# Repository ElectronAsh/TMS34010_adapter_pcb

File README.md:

# TMS34010_adapter_pcb

# USE AT YOUR OWN RISK!

This adapter PCB should allow you to connect a TMS34010 CPU to FPGA dev boards like the DE10 Nano, and maybe the DE0.

But it is currently UNTESTED, and does not include proper voltage translation buffers between 3V3 and 5V.

The current design only has some series resistors on each CPU output pin, with some clamp diodes on the FPGA GPIO headers.

There is an inherent risk of not using proper voltage translation, but I would personally risk it for short-term use for development.

If I get time, I will add proper voltage translation to the board.
The current design was just a way to get a quick version done for the few devs who might be able to make use of it.

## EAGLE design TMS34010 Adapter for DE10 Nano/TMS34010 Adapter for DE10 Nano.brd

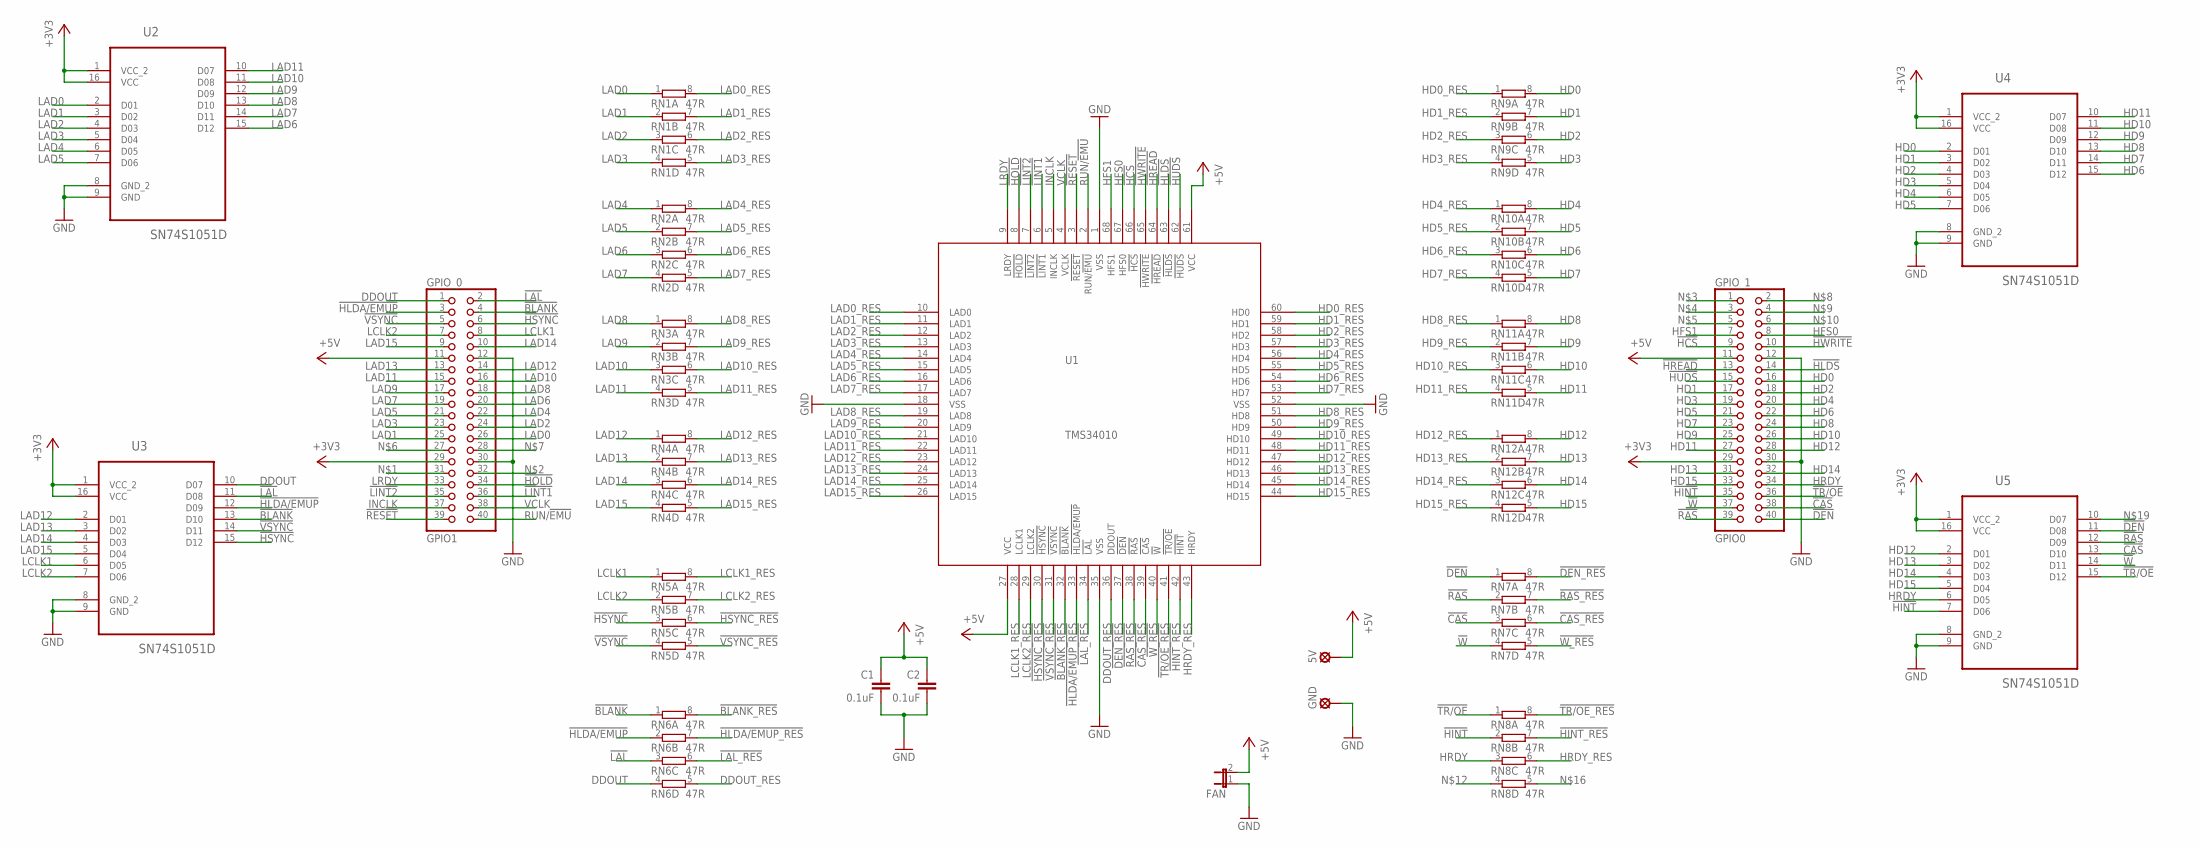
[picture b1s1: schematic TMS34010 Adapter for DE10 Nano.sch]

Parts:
5V: LSP13
C1, C2: 0.1uF; C0603
FAN: JP1E; JP1
GND: LSP13
GPIO_0: GPIO1; 2X20
GPIO_1: GPIO0; 2X20
RN1, RN2, RN3, RN4, RN5, RN6, RN7, RN8, RN9, RN10, RN11, RN12: 47R; EXBV8V
U1: TMS34010; PLCC68
U2, U3, U4, U5: SN74S1051D; SOIC127P600X175-16N

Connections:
!BLANK: GPIO_0.4, RN6.1, U3.13 (D10)
!BLANK_RES: RN6.8 (2), U1.32 (!BLANK)
!CAS: GPIO_1.38, RN7.3 (1), U5.13 (D10)
!CAS_RES: RN7.6 (2), U1.39 (!CAS)
!DEN: GPIO_1.40, RN7.1, U5.11 (D08)
!DEN_RES: RN7.8 (2), U1.37 (!DEN)
!HCS: GPIO_1.9, U1.66 (!HCS)
!HINT: GPIO_1.35, RN8.2 (1), U5.7 (D06)
!HINT_RES: RN8.7 (2), U1.42 (!HINT)
!HLDA/EMUP: GPIO_0.3, RN6.2 (1), U3.12 (D09)
!HLDA/EMUP_RES: RN6.7 (2), U1.33 (!HLDA/EMUP)
!HLDS: GPIO_1.14, U1.63 (!HLDS)
!HOLD: GPIO_0.34, U1.8 (!HOLD)
!HREAD: GPIO_1.13, U1.64 (!HREAD)
!HSYNC: GPIO_0.6, RN5.3 (1), U3.15 (D12)
!HSYNC_RES: RN5.6 (2), U1.30 (!HSYNC)
!HUDS: GPIO_1.15, U1.62 (!HUDS)
!HWRITE: GPIO_1.10, U1.65 (!HWRITE)
!LAL: GPIO_0.2, RN6.3 (1), U3.11 (D08)
!LAL_RES: RN6.6 (2), U1.34 (!LAL)
!LINT1: GPIO_0.36, U1.6 (!LINT1)
!LINT2: GPIO_0.35, U1.7 (!LINT2)
!RAS: GPIO_1.39, RN7.2 (1), U5.12 (D09)
!RAS_RES: RN7.7 (2), U1.38 (!RAS)
!RESET: GPIO_0.39, U1.3 (!RESET)
!TR/OE: GPIO_1.36, RN8.1, U5.15 (D12)
!TR/OE_RES: RN8.8 (2), U1.41 (!TR/OE)
!VSYNC: GPIO_0.5, RN5.4 (1), U3.14 (D11)
!VSYNC_RES: RN5.5 (2), U1.31 (!VSYNC)
!W: GPIO_1.37, RN7.4 (1), U5.14 (D11)
!W_RES: RN7.5 (2), U1.40 (!W)
+3V3: GPIO_0.29, GPIO_1.29, U2.1 (VCC_2), U2.16 (VCC), U3.1 (VCC_2), U3.16 (VCC), U4.1 (VCC_2), U4.16 (VCC), U5.1 (VCC_2), U5.16 (VCC)
+5V: 5V.MP, C1.1, C2.1, FAN.2, GPIO_0.11, GPIO_1.11, U1.27 (VCC), U1.61 (VCC)
DDOUT: GPIO_0.1, RN6.4 (1), U3.10 (D07)
DDOUT_RES: RN6.5 (2), U1.36 (DDOUT)
GND: C1.2, C2.2, FAN.1, GND.MP, GPIO_0.12, GPIO_0.30, GPIO_1.12, GPIO_1.30, U1.1 (VSS), U1.18 (VSS), U1.35 (VSS), U1.52 (VSS), U2.8 (GND_2), U2.9 (GND), U3.8 (GND_2), U3.9 (GND), U4.8 (GND_2), U4.9 (GND), U5.8 (GND_2), U5.9 (GND)
HD0: GPIO_1.16, RN9.8 (2), U4.2 (D01)
HD0_RES: RN9.1, U1.60 (HD0)
HD1: GPIO_1.17, RN9.7 (2), U4.3 (D02)
HD1_RES: RN9.2 (1), U1.59 (HD1)
HD2: GPIO_1.18, RN9.6 (2), U4.4 (D03)
HD2_RES: RN9.3 (1), U1.58 (HD2)
HD3: GPIO_1.19, RN9.5 (2), U4.5 (D04)
HD3_RES: RN9.4 (1), U1.57 (HD3)
HD4: GPIO_1.20, RN10.8 (2), U4.6 (D05)
HD4_RES: RN10.1, U1.56 (HD4)
HD5: GPIO_1.21, RN10.7 (2), U4.7 (D06)
HD5_RES: RN10.2 (1), U1.55 (HD5)
HD6: GPIO_1.22, RN10.6 (2), U4.15 (D12)
HD6_RES: RN10.3 (1), U1.54 (HD6)
HD7: GPIO_1.23, RN10.5 (2), U4.14 (D11)
HD7_RES: RN10.4 (1), U1.53 (HD7)
HD8: GPIO_1.24, RN11.8 (2), U4.13 (D10)
HD8_RES: RN11.1, U1.51 (HD8)
HD9: GPIO_1.25, RN11.7 (2), U4.12 (D09)
HD9_RES: RN11.2 (1), U1.50 (HD9)
HD10: GPIO_1.26, RN11.6 (2), U4.11 (D08)
HD10_RES: RN11.3 (1), U1.49 (HD10)
HD11: GPIO_1.27, RN11.5 (2), U4.10 (D07)
HD11_RES: RN11.4 (1), U1.48 (HD11)
HD12: GPIO_1.28, RN12.8 (2), U5.2 (D01)
HD12_RES: RN12.1, U1.47 (HD12)
HD13: GPIO_1.31, RN12.7 (2), U5.3 (D02)
HD13_RES: RN12.2 (1), U1.46 (HD13)
HD14: GPIO_1.32, RN12.6 (2), U5.4 (D03)
HD14_RES: RN12.3 (1), U1.45 (HD14)
HD15: GPIO_1.33, RN12.5 (2), U5.5 (D04)
HD15_RES: RN12.4 (1), U1.44 (HD15)
HFS0: GPIO_1.8, U1.67 (HFS0)
HFS1: GPIO_1.7, U1.68 (HFS1)
HRDY: GPIO_1.34, RN8.3 (1), U5.6 (D05)
HRDY_RES: RN8.6 (2), U1.43 (HRDY)
INCLK: GPIO_0.37, U1.5 (INCLK)
LAD0: GPIO_0.26, RN1.1, U2.2 (D01)
LAD0_RES: RN1.8 (2), U1.10 (LAD0)
LAD1: GPIO_0.25, RN1.2 (1), U2.3 (D02)
LAD1_RES: RN1.7 (2), U1.11 (LAD1)
LAD2: GPIO_0.24, RN1.3 (1), U2.4 (D03)
LAD2_RES: RN1.6 (2), U1.12 (LAD2)
LAD3: GPIO_0.23, RN1.4 (1), U2.5 (D04)
LAD3_RES: RN1.5 (2), U1.13 (LAD3)
LAD4: GPIO_0.22, RN2.1, U2.6 (D05)
LAD4_RES: RN2.8 (2), U1.14 (LAD4)
LAD5: GPIO_0.21, RN2.2 (1), U2.7 (D06)
LAD5_RES: RN2.7 (2), U1.15 (LAD5)
LAD6: GPIO_0.20, RN2.3 (1), U2.15 (D12)
LAD6_RES: RN2.6 (2), U1.16 (LAD6)
LAD7: GPIO_0.19, RN2.4 (1), U2.14 (D11)
LAD7_RES: RN2.5 (2), U1.17 (LAD7)
LAD8: GPIO_0.18, RN3.1, U2.13 (D10)
LAD8_RES: RN3.8 (2), U1.19 (LAD8)
LAD9: GPIO_0.17, RN3.2 (1), U2.12 (D09)
LAD9_RES: RN3.7 (2), U1.20 (LAD9)
LAD10: GPIO_0.16, RN3.3 (1), U2.11 (D08)
LAD10_RES: RN3.6 (2), U1.21 (LAD10)
LAD11: GPIO_0.15, RN3.4 (1), U2.10 (D07)
LAD11_RES: RN3.5 (2), U1.22 (LAD11)
LAD12: GPIO_0.14, RN4.1, U3.2 (D01)
LAD12_RES: RN4.8 (2), U1.23 (LAD12)
LAD13: GPIO_0.13, RN4.2 (1), U3.3 (D02)
LAD13_RES: RN4.7 (2), U1.24 (LAD13)
LAD14: GPIO_0.10, RN4.3 (1), U3.4 (D03)
LAD14_RES: RN4.6 (2), U1.25 (LAD14)
LAD15: GPIO_0.9, RN4.4 (1), U3.5 (D04)
LAD15_RES: RN4.5 (2), U1.26 (LAD15)
LCLK1: GPIO_0.8, RN5.1, U3.6 (D05)
LCLK1_RES: RN5.8 (2), U1.28 (LCLK1)
LCLK2: GPIO_0.7, RN5.2 (1), U3.7 (D06)
LCLK2_RES: RN5.7 (2), U1.29 (LCLK2)
LRDY: GPIO_0.33, U1.9 (LRDY)
RUN/!EMU: GPIO_0.40, U1.2 (RUN/!EMU)
VCLK: GPIO_0.38, U1.4 (VCLK)

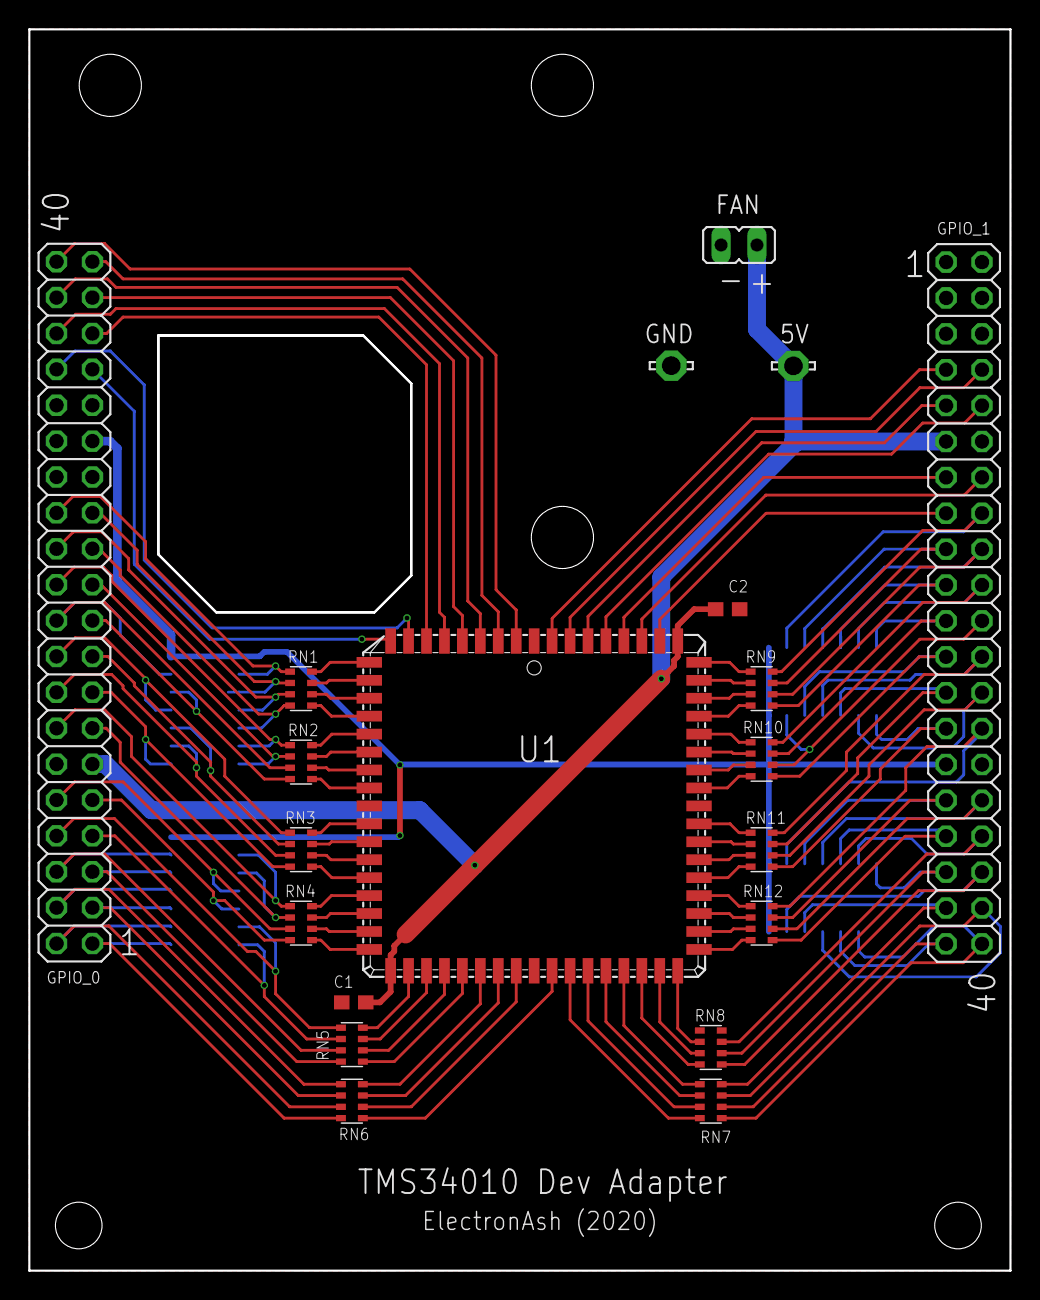
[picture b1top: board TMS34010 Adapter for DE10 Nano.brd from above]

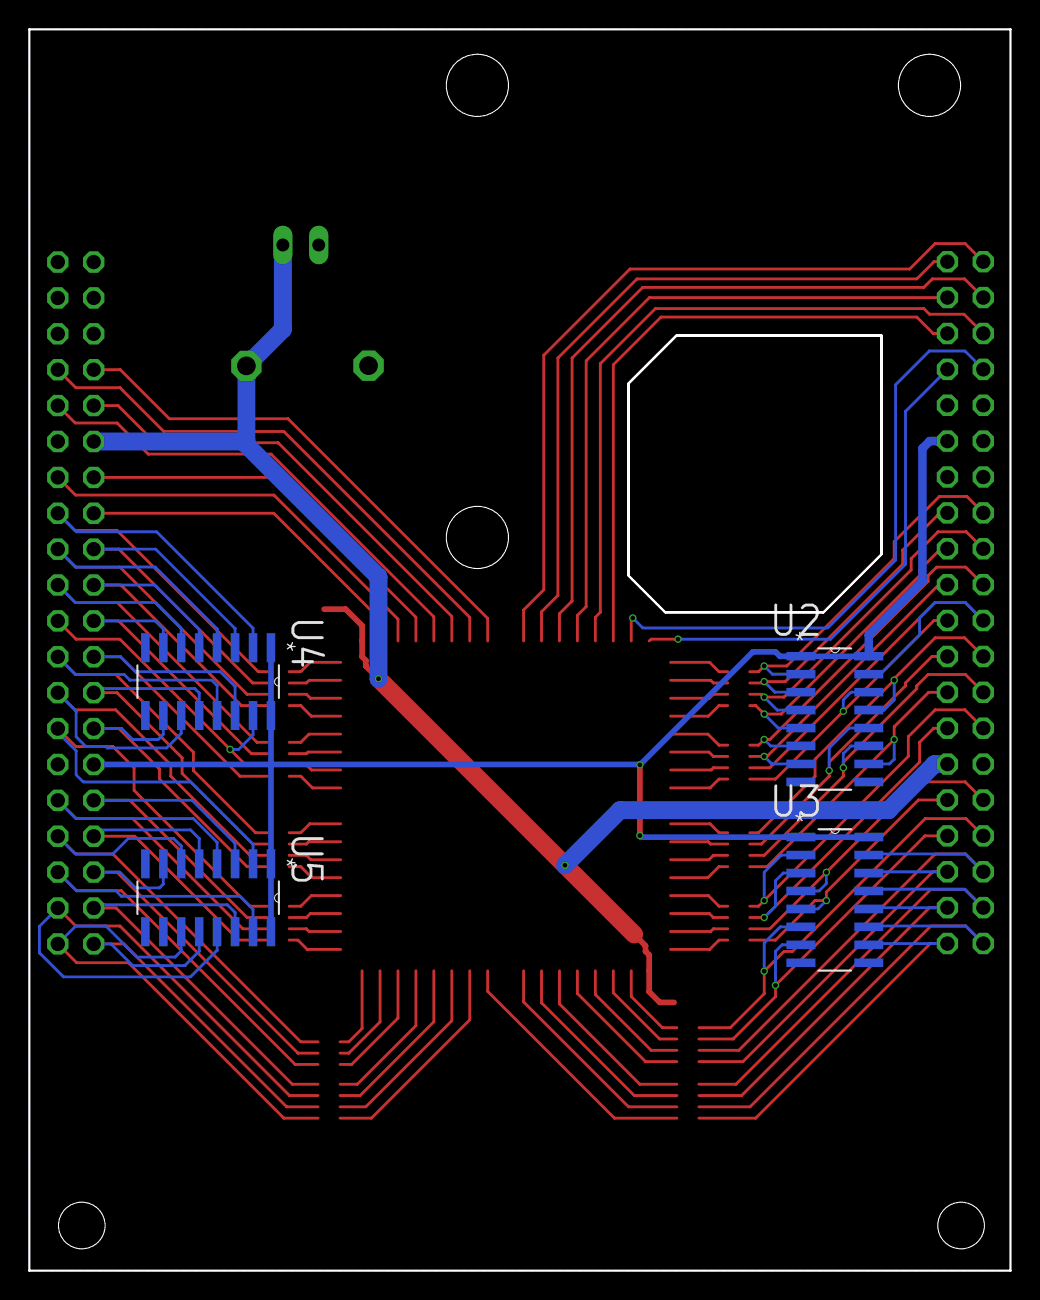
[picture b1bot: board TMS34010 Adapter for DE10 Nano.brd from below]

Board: 2 copper layers, 69.4 x 87.9 mm, 24 parts (4 on the bottom side), 112 nets.

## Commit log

2020-07-30 add README and images
2020-07-30 update image links
